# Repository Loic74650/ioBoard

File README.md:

<h2>ioBoard v1.2</h2>
<h2>I/O board with Ethernet connectivity for home automation applications</h2>
<br />
 <br /><br />
<br />
<h4>Brief description</h4>
<p>Simply put, ioBoard is a mix between an Arduino Mega board, the Ethernet shield and the relay shield + some small additional features (RTC, opto-isolation of digital inputs/outputs, two analog inputs, one Teleinfo input…).<br />
It supports the MQTT protocol and has a set of API functions so that it is easy to control it over the Ethernet for home automation applications for instance.<br />
ioBoard can be programmed to perform tasks at regular intervals such as water the garden or switch on a pump autonomously. <br />
ioBoard also has input pulse counters, typically used to track the consumption of a gas or oil heater, water or even electrical consumption.<br />
ioBoard also has a TeleInfo input, which is a French dedicated energy meter interface to the main electric meter of the house.<br />
Finally, ioBoard has a small web server stored on an SD card, in order to reflect the status of the board I/Os.</p> <br />

<h4>Main specs:</h4>
<p>
<ul>
<li>Atmega2560 16MHz µC</li>
<li>programmable with Arduino IDE (with USB interface)</li>
<li>Ethernet 10M/100M RJ45 internet interface</li>
<li>x8 Relay outputs 230VAC/30VDC 10A – Form-C relays, screw terminal and SMD Status-LED for each (opto-isolated from µC)</li>
<li>x8 opto-isolated digital inputs with SMD Status-LEDs (internal pull-up, HIGH level by default. Ground the input to make it LOW)</li> 
<li>x2 10 bits analog inputs 0-3.3VDC</li>
<li>x2 opto-isolated digital input pulse counters (internal pull-up by default. Ground the input to increment it. Input low-pass filtered at 10Hz max.)</li> 
<li>x1 opto-isolated Télé-Info input</li> 
<li>RTC module (DS1307) for time management with on-board Lithium back-up battery</li> 
<li>Micro SD card slot (Web server) </li>
<li>DIN rail format (PCB Size 143mm x 72mm)</li>
</ul>
</p><br />

<h4>Getting started</h4>
<p>
Before compiling the code and flashing it onto the µC, make sure you have changed the following variables in the code:<br /> 
<ul>
<li>MAC address of the board</li>
<li>IP address of the MQTT broker</li>
<li>Credentials to log into the MQTT broker</li>
</ul>
</p><br />

<h4>MQTT API</h4>
<p>
Below are the Payloads/commands to publish on the "ioBoard/API" topic in Json format in order to launch actions on the ioBoard:<br />
<ul>
<li>{"SetRelayMode":[3,1,500]} -> set the operating mode for a relay. 0 is standard operating mode (ON/OFF) and 1 is PULSE mode. In pulse mode, after a relay has been switched ON, it will automatically switch back to OFF state after a defined time in millisecs. In this example, relay #3 is set to PULSE mode with a switch back time of 500ms</li> 
<li>{"SetRelay":[4,1]}      -> set state of a defined relay. In this example, relay #4 is set to 1</li> 
<li>{"SetRelays":15}        -> set all relays states at once by sending a Byte. Each individual bit reflects the status of one relay. In this example, the first four relays are switched ON and the last four are switched OFF (15 in decimal form corresponds to 00001111 in binary form)</li> 
<li>{"SetC0":0}        		-> set initial value of Counter #0</li>
<li>{"SetC1":2140}        	-> set initial value of Counter #1</li>
<li>{"SetDate":[1,1,1,18,13,32,0]}      -> set date/time of RTC module in the following format: (Day of the month, Day of the week, Month, Year, Hour, Minute, Seconds), in this example: Monday 1st January 2018 - 13h32mn00secs</li>
</ul>
<br />

The status of the I/Os is published on the "ioBoard/IOs" topic in the following Json format:<br />
<ul>
<li>{"Relays":15}       	-> A Byte representing all the relays states. Each individual bit reflects the status of one relay. In this example, the first four relays are ON and the last four are OFF (15 in decimal form corresponds to 00001111 in binary form)</li>
<li>{"DIns":127}       		-> A Byte representing all the digital input states. Each individual bit reflects the status of one input. In this example, the first input state is FALSE and the last seven are TRUE (127 in decimal form corresponds to 01111111 in binary form)</li>
<li>{"C0":1203}       		-> Value of Counter0</li>
<li>{"C1":0}       			-> Value of Counter1</li>
<li>{"AI":[1203,0]}       	-> Values of the Analog Inputs. In this example, AI0 is 1203 and AI1 is 0</li>
<li>{"TI":[ADCO,OPTARIF,ISOUSC,BASE,IINST,PAPP,ADPS,IMAX,PTEC]}      -> TeleInfo data. Refer to this link for more info: https://www.enedis.fr/sites/default/files/Enedis-NOI-CPT_02E.pdf</li>
</ul>
<br />

The above Json commands representing the state of the I/Os are updated as soon as a Digital I/O changes state or every 30 secs for the Analog Inputs.
</p><br />

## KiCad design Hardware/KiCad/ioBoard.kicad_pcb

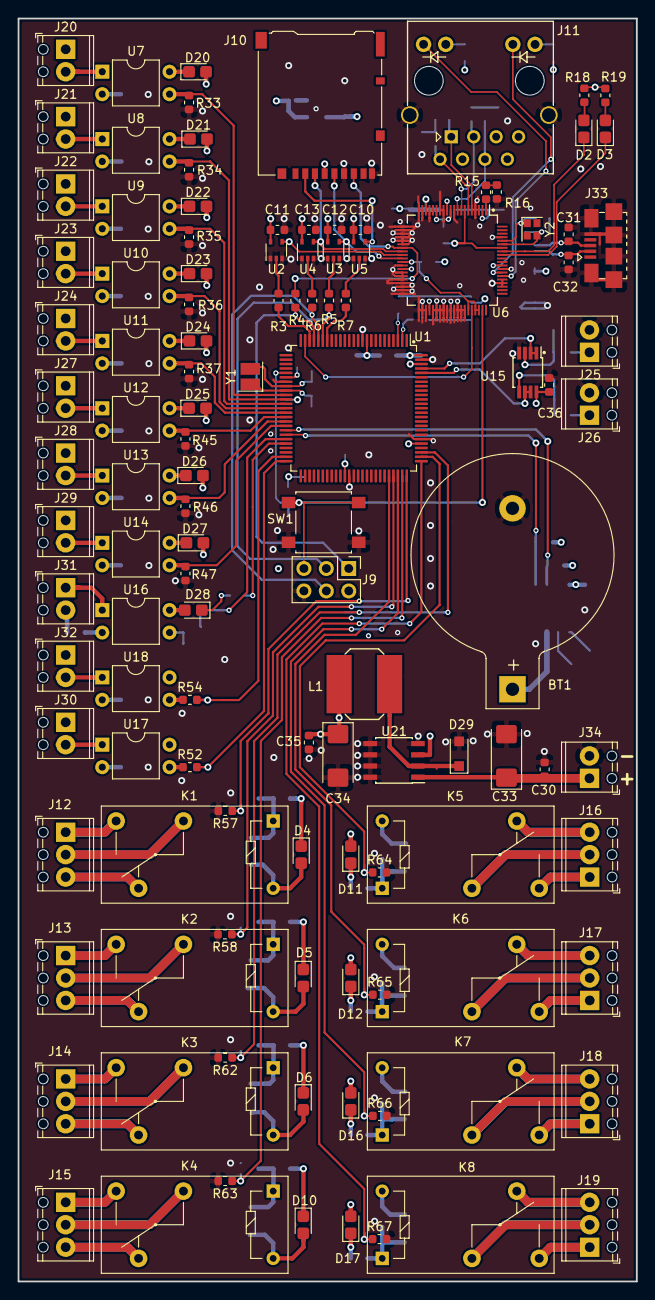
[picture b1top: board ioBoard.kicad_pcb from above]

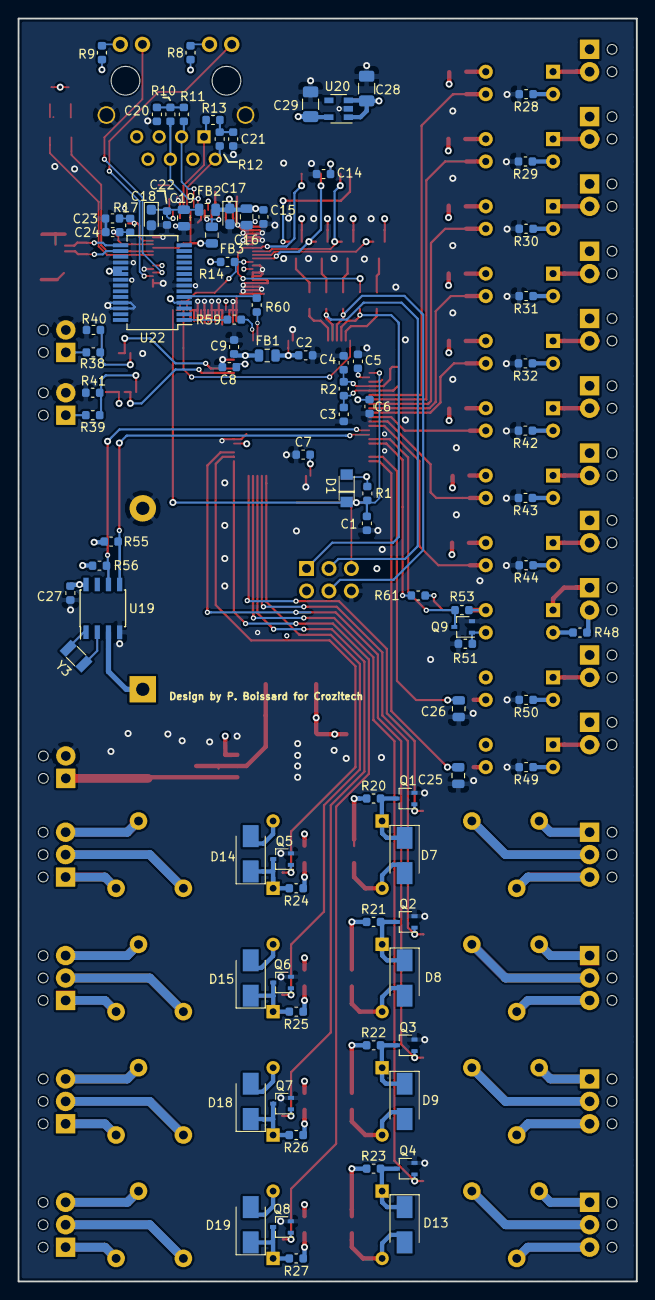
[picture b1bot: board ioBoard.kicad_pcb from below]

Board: 4 copper layers, 70.0 x 143.0 mm, 206 parts (90 on the bottom side), 159 nets.

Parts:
BT1: CR2025; BatteryHolder_Keystone_103_1x20mm
C1, C23, C24: 22pF; C_0603_1608Metric
C2, C5, C6, C7, C8, C9, C14, C15, C20, C21, C22, C27, C30, C35, C36: 100nF; C_0603_1608Metric
C3, C4: 15pF; C_0603_1608Metric
C10, C11, C12, C13: 10nF; C_0603_1608Metric
C16, C19: 1uF; C_0805_2012Metric
C17, C18: 10µF; CP_EIA-2012-15_AVX-P
C25, C26: 1µF; C_0805_2012Metric
C28, C29: 1µF; C_1206_3216Metric
C31, C32: 47pF; C_0603_1608Metric
C33, C34: 10µF; CP_EIA-6032-15_Kemet-U
D1: RSFBL-R3; D_Sub_SMA
D2, D3, D4, D5, D6, D10, D11, D12, D16, D17, D20, D21, D22, D23, D24, D25, D26, D27, D28: LED; LED_0805_2012Metric_Castellated
D7, D8, D9, D13, D14, D15, D18, D19: S1JL R3; D_SMA
D29: NRVTS2H60ESFT3G; D_SOD-123F
FB1: 10µH; L_0805_2012Metric
FB2, FB3: MH2029-300Y; L_0805_2012Metric
J9: ICSP; PinHeader_2x03_P2.54mm_Vertical
J10: Micro_SD_Card; microSD_HC_Hirose_DM3AT-SF-PEJM5
J11: 8P8C_LED_Shielded; RJ45_Stewart_SS_74301_001
J12, J13, J14, J15, J16, J17, J18, J19: MPT 0.5/3-2.54; TerminalBlock_Phoenix_MPT-0,5-3-2.54_1x03_P2.54mm_Horizontal
J20: MPT 0.5/2-2.54; TerminalBlock_Phoenix_MPT-0,5-2-2.54_1x02_P2.54mm_Horizontal
J21, J22, J23, J24, J25, J26, J27, J28, J29, J30, J31, J32, J34: MPT 0.5/3-2.54; TerminalBlock_Phoenix_MPT-0,5-2-2.54_1x02_P2.54mm_Horizontal
J33: USB_B_Micro; USB_Micro-B_Amphenol_110118192-0001LF_Horizontal
K1, K2, K3, K4, K5, K6, K7, K8: G5Q-1EU; Relay_SPDT_Omron-G5Q-1
L1: 47µH; L_Bourns-SRU8043
Q1, Q2, Q3, Q4, Q5, Q6, Q7, Q8, Q9: RU1C001UNTCL; SOT-323_SC-70
R1, R14, R38, R39, R40, R41, R51, R53, R55, R56, R57, R58, R62, R63, R64, R65, R66, R67: 10K; R_0603_1608Metric
R2, R17: 1M; R_0603_1608Metric
R3, R4, R5, R6, R7, R59, R60: 100; R_0603_1608Metric
R8, R9, R18, R19: 1K; R_0603_1608Metric
R10, R11, R12, R13: 49.9; R_0603_1608Metric
R15: 12K; R_0603_1608Metric
R16: 300; R_0603_1608Metric
R20, R21, R22, R23, R24, R25, R26, R27: 5K; R_0603_1608Metric
R28, R29, R30, R31, R32, R42, R43, R44, R49, R50: 520; R_0603_1608Metric
R33, R34, R35, R36, R37, R45, R46, R47, R61: 1K5; R_0603_1608Metric
R48: 4.7K; R_0603_1608Metric
R52, R54: 15K; R_0603_1608Metric
SW1: SW_DPST; SW_SPST_B3S-1000
U1: ATmega2560; TQFP-100_14x14mm_P0.5mm
U2, U3, U4, U5: 74AHC1G125; SOT-353_SC-70-5
U6: W5100; LQFP-80_10x10mm_P0.4mm
U7, U8, U9, U10, U11, U12, U13, U14, U17, U18: SFH617A-1; DIP-4_W7.62mm
U15: LM2904; MSOP-8_3x3mm_P0.65mm
U16: SFH620A; DIP-4_W7.62mm
U19: DS1307+; SOIC-8_3.9x4.9mm_P1.27mm
U20: MIC5504-3.3YM5; SOT-23-5
U21: AP1509; SOIC-8_3.9x4.9mm_P1.27mm
U22: FT232RL; SSOP-28_5.3x10.2mm_P0.65mm
Y1: 16MHz; Crystal_SMD_2520-4Pin_2.5x2.0mm
Y2: 25MHz; Crystal_SMD_2016-4Pin_2.0x1.6mm
Y3: 32.768KHz; Crystal_SMD_3215-2Pin_3.2x1.5mm

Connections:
+1V8: FB3.1, U6.11, U6.15, U6.16, U6.33, U6.69
+3.3VA: C18.1, C19.1, C22.1, FB2.2, U6.2
+3V3: C10.1, C11.1, C12.1, C13.1, C14.1, C15.1, C16.1, C17.1, C29.1, FB2.1, J10.4, R8.1, R9.1, R14.2, R18.1, R19.1, U2.5, U3.5, U4.5, U5.5, U6.12, U6.18, U6.44, U20.5
+5V: C2.2, C5.2, C6.2, C7.2, C27.2, C28.1, C34.1, C35.1, C36.1, D1.2, D20.2, D21.2, D22.2, D23.2, D24.2, D25.2, D26.2, D27.2, D28.2, FB1.2, J9.2, L1.2, R1.1, R53.2, R55.1, R56.1, U1.10, U1.31, U1.61, U1.80, U15.8, U16.4, U17.4, U18.4, U19.8, U20.1, U20.3, U21.3, U22.4, U22.19, U22.20
+5VA: C9.2, FB1.1, U1.100
+12V: C30.1, C33.1, D4.2, D5.2, D6.2, D7.2, D8.2, D9.2, D10.2, D11.2, D12.2, D13.2, D14.2, D15.2, D16.2, D17.2, D18.2, D19.2, J20.1, J21.1, J22.1, J23.1, J24.1, J27.1, J28.1, J29.1, J30.1, J32.1, J34.1, K1.5, K2.5, K3.5, K4.5, K5.5, K6.5, K7.5, K8.5, U21.1
+BATT: BT1.1, U19.3
/ADC_0: U1.97, U15.1, U15.2
/ADC_1: U1.96, U15.6, U15.7
/COUNTER_0: C25.1, R52.2, U1.50
/COUNTER_1: C26.1, R54.2, U1.49
/CS_ETH: U2.4, U6.29
/CS_SDCARD: J10.2, U5.4
/Ethernet/LINKLED: J11.9, U6.66
/Ethernet/RX+: J11.1, R13.1, U6.5
/Ethernet/RX-: J11.2, R12.2, U6.6
/Ethernet/SPDLED: J11.11, U6.67
/Ethernet/TX+: J11.3, R11.1, U6.8
/Ethernet/TX-: J11.6, R10.2, U6.9
/ICSP_MISO: J9.1, R4.1, U1.22
/ICSP_MOSI: J9.4, R6.1, U1.21
/ICSP_SCK: J9.3, R5.1, U1.20
/ITOR_0: R33.1, U1.35, U7.3
/ITOR_1: R34.1, U1.36, U8.3
/ITOR_2: R35.1, U1.37, U9.3
/ITOR_3: R36.1, U1.38, U10.3
/ITOR_4: R37.1, U1.39, U11.3
/ITOR_5: R45.1, U1.40, U12.3
/ITOR_6: R46.1, U1.41, U13.3
/ITOR_7: R47.1, U1.42, U14.3
/LED_TELEINFO: R61.1, U1.46
/MISO: J10.7, R4.2, U6.27
/MOSI: J10.3, U4.4, U6.28
/PCINT5: U1.24, U6.56
/RST: C1.2, D1.1, J9.5, R1.2, SW1.1, SW1.3, U1.30, U6.59
/RXD0: R59.1, U1.2
/RXD1: Q9.3, R53.1, U1.45
/SCK: J10.5, U3.4, U6.30
/SCL: R56.2, U1.43, U19.6
/SDA: R55.2, U1.44, U19.5
/STOR_0: Q3.1, R62.1, U1.78
/STOR_1: Q5.1, R64.1, U1.77
/STOR_2: Q8.1, R67.1, U1.76
/STOR_3: Q1.1, R57.1, U1.75
/STOR_4: Q4.1, R63.1, U1.74
/STOR_5: Q7.1, R66.1, U1.73
/STOR_6: Q2.1, R58.1, U1.72
/STOR_7: Q6.1, R65.1, U1.71
/TXD0: R60.2, U1.3
Earth: BT1.2, C1.1, C2.1, C3.1, C4.1, C5.1, C6.1, C7.1, C8.2, C9.1, C10.2, C11.2, C12.2, C13.2, C14.2, C15.2, C16.2, C17.2, C18.2, C19.2, C20.2, C21.2, C22.2, C23.1, C24.1, C25.2, C26.2, C27.1, C28.2, C29.2, C30.2, C31.1, C32.1, C33.2, C34.2, C35.2, C36.2, D29.2, J9.6, J10.6, J10.9, J11.SH, J25.2, J26.2, J33.5, J33.6, J34.2, Q1.2, Q2.2, Q3.2, Q4.2, Q5.2, Q6.2, Q7.2, Q8.2, Q9.2, R16.2, R28.2, R29.2, R30.2, R31.2, R32.2, R33.2, R34.2, R35.2, R36.2, R37.2, R40.2, R41.2, R42.2, R43.2, R44.2, R45.2, R46.2, R47.2, R49.2, R50.2, R51.1, R57.2, R58.2, R62.2, R63.2, R64.2, R65.2, R66.2, R67.2, SW1.2, SW1.4, U1.11, U1.32, U1.62, U1.81, U1.99, U2.1, U2.3, U3.1, U3.3, U4.1, U4.3, U5.1, U5.3, U6.4, U6.10, U6.13, U6.14, U6.17, U6.19, U6.20, U6.21, U6.22, U6.23, U6.24, U6.25, U6.26, U6.32, U6.34, U6.35, U6.36, U6.37, U6.38, U6.39, U6.40, U6.41, U6.42, U6.43, U6.45, U6.46, U6.47, U6.48, U6.49, U6.50, U6.51, U6.52, U6.53, U6.54, U6.63, U6.64, U6.65, U6.68, U6.77, U15.4, U19.4, U20.2, U21.4, U21.5, U21.6, U21.7, U21.8, U22.7, U22.18, U22.21, U22.25, U22.26
unnamed: C3.2, R2.1, U1.34, Y1.1
unnamed: C4.2, R2.2, U1.33, Y1.2
unnamed: C8.1, U1.98
unnamed: C20.1, R10.1, R11.2
unnamed: C21.1, R12.1, R13.2
unnamed: C23.2, R17.1, U6.76, Y2.1
unnamed: C24.2, R17.2, U6.75, Y2.3
unnamed: C31.2, J33.3, U22.15
unnamed: C32.2, J33.2, U22.16
unnamed: D2.1, U6.73
unnamed: D2.2, R18.2
unnamed: D3.1, U6.72
unnamed: D3.2, R19.2
unnamed: D4.1, R20.1
unnamed: D5.1, R21.1
unnamed: D6.1, R22.1
unnamed: D7.1, K1.1, Q1.3, R20.2
unnamed: D8.1, K2.1, Q2.3, R21.2
unnamed: D9.1, K3.1, Q3.3, R22.2
unnamed: D10.1, R23.1
unnamed: D11.1, R24.1
unnamed: D12.1, R25.1
unnamed: D13.1, K4.1, Q4.3, R23.2
unnamed: D14.1, K5.1, Q5.3, R24.2
unnamed: D15.1, K6.1, Q6.3, R25.2
unnamed: D16.1, R26.1
unnamed: D17.1, R27.1
unnamed: D18.1, K7.1, Q7.3, R26.2
unnamed: D19.1, K8.1, Q8.3, R27.2
unnamed: D20.1, U7.4
unnamed: D21.1, U8.4
unnamed: D22.1, U9.4
unnamed: D23.1, U10.4
unnamed: D24.1, U11.4
unnamed: D25.1, U12.4
unnamed: D26.1, U13.4
unnamed: D27.1, U14.4
unnamed: D28.1, R61.2
unnamed: D29.1, L1.1, U21.2
unnamed: FB3.2, U6.7, U6.74
unnamed: J11.10, R8.2
unnamed: J11.12, R9.2
unnamed: J12.1, K1.3
unnamed: J12.2, K1.2
unnamed: J12.3, K1.4
unnamed: J13.1, K2.3
unnamed: J13.2, K2.2
unnamed: J13.3, K2.4
unnamed: J14.1, K3.3
unnamed: J14.2, K3.2
unnamed: J14.3, K3.4
unnamed: J15.1, K4.3
unnamed: J15.2, K4.2
unnamed: J15.3, K4.4
unnamed: J16.1, K5.3
unnamed: J16.2, K5.2
unnamed: J16.3, K5.4
unnamed: J17.1, K6.3
unnamed: J17.2, K6.2
unnamed: J17.3, K6.4
unnamed: J18.1, K7.3
unnamed: J18.2, K7.2
unnamed: J18.3, K7.4
unnamed: J19.1, K8.3
unnamed: J19.2, K8.2
unnamed: J19.3, K8.4
unnamed: J20.2, U7.1
unnamed: J21.2, U8.1
unnamed: J22.2, U9.1
unnamed: J23.2, U10.1
unnamed: J24.2, U11.1
unnamed: J25.1, R38.1
unnamed: J26.1, R39.1
unnamed: J27.2, U12.1
unnamed: J28.2, U13.1
unnamed: J29.2, U14.1
unnamed: J30.2, U17.1
unnamed: J31.1, U16.1
unnamed: J31.2, R48.1
unnamed: J32.2, U18.1
unnamed: Q9.1, R51.2, U16.3
unnamed: R3.1, U1.23
unnamed: R3.2, U2.2
unnamed: R5.2, U3.2
unnamed: R6.2, U4.2
unnamed: R7.1, U1.19
unnamed: R7.2, U5.2
unnamed: R14.1, U6.31, U6.55, U6.57, U6.58
unnamed: R15.1, U6.1
unnamed: R15.2, R16.1
unnamed: R28.1, U7.2
unnamed: R29.1, U8.2
unnamed: R30.1, U9.2
unnamed: R31.1, U10.2
unnamed: R32.1, U11.2
unnamed: R38.2, R40.1, U15.3
unnamed: R39.2, R41.1, U15.5
unnamed: R42.1, U12.2
unnamed: R43.1, U13.2
unnamed: R44.1, U14.2
unnamed: R48.2, U16.2
unnamed: R49.1, U17.2
unnamed: R50.1, U18.2
unnamed: R52.1, U17.3
unnamed: R54.1, U18.3
unnamed: R59.2, U22.1
unnamed: R60.1, U22.5
unnamed: U19.1, Y3.1
unnamed: U19.2, Y3.2

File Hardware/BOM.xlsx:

Date: | 43635
Tool: | Eeschema (5.0.2)-1
Generator: | C:\Program Files\KiCad\bin\scripting\plugins/bom_csv_grouped_by_value_with_fp.py
Component Count: | 188
Ref | Qnty | Value | Cmp name | Footprint | Description | Farnel n° | Prix unitaire | Total
 | 1 | CR2025 | Battery_Cell |  | ~ | 2065170 | 0.52400000000000002 | 0.52400000000000002
BT1 | 1 | 103 | KEYSTONE |  |  | 676469 | 2.79 | 2.79
C1, C23, C24, | 3 | 22pF | C |  | Unpolarized capacitor | 2309012 | 5.4899999999999997E-2 | 0.16469999999999999
C3, C4, | 2 | 15pF | C |  | Unpolarized capacitor | 1759055 | 4.5499999999999999E-2 | 9.0999999999999998E-2
C7, C6, C5, C2, C9, C8, C14, C21, C20, C15, C22, C27, C30, C35, C36 | 14 | 100nF | C |  | Unpolarized capacitor | 2210925 | 4.6300000000000001E-2 | 0.6482
C12, C10, C13, C11, | 4 | 10nF | C |  | Unpolarized capacitor | 9406182 | 2.0199999999999999E-2 | 8.0799999999999997E-2
C16, C19, C25, C26, | 4 | 1uF | C |  | Unpolarized capacitor | 2896564 | 6.1699999999999998E-2 | 0.24679999999999999
C31, C32, | 2 | 47pF | C |  | Unpolarized capacitor | 1759062 | 4.9700000000000001E-2 | 9.9400000000000002E-2
C29, C28, | 2 | 1µF | CP |  | Polarized capacitor | 2491457 | 0.24399999999999999 | 0.48799999999999999
C33, C34 | 2 | 10µF | CP |  | Polarized capacitor | 2462775 | 0.217 | 0.434
C17, C18, | 2 | 10µF | CP |  | Polarized capacitor | 2491430 | 0.313 | 0.626
D1, | 1 | RSFBL R3 | DIODE |  | Diode symbol for simulation only. Pin order incompatible with official kicad fo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 | 1559142 | 8.7400000000000005E-2 | 8.7400000000000005E-2
D2, D3, D6, D11, D10, D16, D5, D12, D17, D4, D20, D21, D22, D23, D24, D25, D26,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 | 19 | LED | KP-2012LSGC |  | Light emitting diode | 2463991 | 8.8200000000000001E-2 | 1.6758
D9, D14, D13, D18, D8, D15, D19, D7, | 8 | S1JL R3 | DIODE |  | Diode symbol for simulation only. Pin order incompatible with official kicad fo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 | 1559153 | 7.0000000000000007E-2 | 0.56000000000000005
D29 | 1 | NRVTS2H60ESFT3G |  |  |  | 3003776 | 0.17899999999999999 | 0.17899999999999999
FB1, | 1 | 10 µH | Ferrite_Bead_Small |  | Ferrite bead, small symbol | 2215650 | 0.11 | 0.11
FB3, FB2, | 2 | MH2029-300Y | Ferrite_Bead_Small |  | Ferrite bead, small symbol | 2859248 | 6.7299999999999999E-2 | 0.1346
J9, | 1 | ICSP | Conn_02x03_Odd_Even |  | Generic connector, double row, 02x03, odd/even pin numbering scheme (row 1 odd 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 | 2473349 | 0.27200000000000002 | 0.27200000000000002
J10, | 1 | Micro_SD_Card | Micro_SD_Card |  | Micro SD Card Socket | 2427719 | 1.83 | 1.83
J11, | 1 | 8P8C_LED_Shielded | 8P8C_LED_Shielded |  | RJ connector, 8P8C (8 positions 8 connected), two LEDs, RJ45, Shielded | 2891063 | 1.22 | 1.22
J14, J16, J15, J18, J13, J17, J19, J12, | 8 | MPT 0.5/3-2.54 | Screw_Terminal_01x03 |  | Generic screw terminal, single row, 01x03, script generated (kicad-library-util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 | 3041360 | 1.02 | 8.16
J20, J21, J22, J23, J24, J27, J28, J29, J25, J26, J30, J32, J31, J34 | 14 | MPT 0.5/2-2.54 | Screw_Terminal_01x02 |  | Generic screw terminal, single row, 01x02, script generated (kicad-library-util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 | 3041359 | 0.72399999999999998 | 10.135999999999999
J33, | 1 | micro USB | micro USB |  |  | 2751674 | 0.26500000000000001 | 0.26500000000000001
K3, K5, K4, K7, K2, K6, K8, K1, | 8 | OMI-SH-112LM | G5Q-1EU |  | Ultra-miniature, Highly Sensitive SPDT Relay for Signal Circuits | 4446434 | 0.77900000000000003 | 6.2320000000000002
L1 | 1 | 47µH | SRU8043 |  |  | 2859240 | 0.77900000000000003 | 0.77900000000000003
Q3, Q5, Q4, Q7, Q2, Q6, Q8, Q1, Q9, | 9 | RU1C001UNTCL | Q_NMOS_GSD |  | N-MOSFET transistor, gate/source/drain | 2706680 | 8.8599999999999998E-2 | 0.7974
R1, R38, R40, R39, R41,R53, R56, R55, R57, R58, R62, R63, R64, R65, R66, R67 | 18 | 10K | R |  | Resistor | 2447230 | 9.7999999999999997E-3 | 0.1764
R2, R17, | 2 | 1M | R |  | Resistor | 2073358 |  | 0
R5, R7, R4, R6, R3, R14, R59, R60, | 8 | 100 | R |  | Resistor | 2694684 | 0.01 | 0.08
R9, R8, R18, R19, R22, R24, R23, R26, R21, R25, R27, R20, | 11 | 1K | R |  | Resistor | 2694685 | 8.2000000000000007E-3 | 9.0200000000000002E-2
R13, R12, R11, R10, | 4 | 49.9 | R |  | Resistor | 2447381 | 9.7999999999999997E-3 | 3.9199999999999999E-2
R15, | 1 | 12K | R |  | Resistor | 2447243 | 9.9000000000000008E-3 | 9.9000000000000008E-3
R16, | 1 | 300 | R |  | Resistor | 2073463 | 8.6999999999999994E-3 | 8.6999999999999994E-3
R28, R29, R30, R31, R32, R42, R43, R44, R49, R50, | 10 | 510 | R |  | Resistor | 1469826 | 9.7999999999999997E-3 | 9.8000000000000004E-2
R33, R34, R35, R37, R45, R46, R47, R36, R51 | 9 | 1K5 | R |  | Resistor | 2694727 | 9.7999999999999997E-3 | 8.8200000000000001E-2
R48, | 1 | 4.7K | R |  | Resistor | 2447385 | 9.4000000000000004E-3 | 9.4000000000000004E-3
R54, R52 | 1 | 15K | R |  | Resistor | 2861871 | 9.9000000000000008E-3 | 9.9000000000000008E-3
SW1, | 1 | SW_DPST | SW_DPST |  | Double Pole Single Throw (DPST) Switch | 1181017 | 0.63100000000000001 | 0.63100000000000001
U1, | 1 | ATmega2560 | ATmega2560-16AU |  | 16MHz, 256kB Flash, 8kB SRAM, 4kB EEPROM, JTAG, TQFP-100 | 1288330 | 10.130000000000001 | 10.130000000000001
U3, U5, U2, U4, | 4 | 74AHC1G125 | 74AHC1G125 |  | Single Buffer Gate Tri-State, Low-Voltage CMOS | 1893809 | 0.20300000000000001 | 0.81200000000000006
U6, | 1 | W5100 | W5100 |  | 10/100Mb Ethernet controller with TCP/IP stack, LQFP-80 |  |  | 5.13
U7, U8, U9, U10, U11, U12, U13, U14, U17, U18, | 10 | SFH617A-1 | SFH617A-1 |  | Optocoupler, Phototransistor Output, 5300 VRMS, VCEO 70V, CTR% 40-80, -55 to +1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 | 1612481 | 0.26100000000000001 | 2.6100000000000003
U16, | 1 | SFH620A-1 | SFH620A-1 |  | Optocoupler, Phototransistor Output, 5300 VRMS, VCEO 70V, CTR% 40-80, -55 to +1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 | 1683360 | 0.72499999999999998 | 0.72499999999999998
U15, | 1 | LM2904 | LM2904 |  | Low-Power, Dual-Operational Amplifiers, DIP-14/SOIC-14/SSOP-14 | 2709555 | 0.185 | 0.185
U19, | 1 | DS1307+ | DS1307+ |  | 64 x 8, Serial, I2C Real-time clock, 4.5V to 5.5V VCC, 0Â°C to +70Â°C, DIP-8 | 2798723 | 2.81 | 2.81
U20, | 1 | MIC5504-3.3YM5 | MIC5504-3.3YM5 |  | 300mA Low-dropout Voltage Regulator, Vout 3.3V, Vin up to 5.5V, SOT-23 | 2510377 | 9.7000000000000003E-2 | 9.7000000000000003E-2
U21, | 1 | AP1509 | AP1509 |  |  | 1825323 | 1.18 | 1.18
U22, | 1 | FT232RL | FT232RL |  |  | 1146032 | 3.93 | 3.93
Y1, | 1 | 16MHz | Crystal |  | Two pin crystal | 2909954 | 0.746 | 0.746
Y2, | 1 | 25MHz | Crystal |  | Two pin crystal | 2909963 | 0.35399999999999998 | 0.35399999999999998
Y3, | 1 | 32.768KHz | Crystal |  | Two pin crystal | 2819305 | 0.34300000000000003 | 0.34300000000000003
 |  |  |  |  |  |  | TOTAL | 65.610000000000028

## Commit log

2019-06-15 Update LICENSE
2019-07-30 First hardware commit
2019-07-30 3D pics
2019-07-30 update pic
2019-11-03 V1.2
